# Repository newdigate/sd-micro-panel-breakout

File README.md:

# sd-micro panel-mount breakout/extender

## option 1 
 * https://github.com/dgouramanis/usdextendercable
   * Dean Gouramanis has done a much better job 
   * unforunately, nothing to mount pcb against front panel
   
## option 2
 * https://github.com/newdigate/usdextendercable
   * Based on the work above - I've extended the female board with 4 M2.5 mounting holes
 
## warning: untested concept work-in-progress, use with caution...

## why
I have a micro-controller mounted behind a front panel. The sd-card reader is fixed to the micro-controller board and is unaccessable to the user. I'd like to allow the user to access the sd-card reader via the front panel. 

I didn't have much success looking for panel mount sd-card extenders unfortunately. There does seems to be a micro-sd extender commonly available, but it doesnt seem to have any way to mount it at a right-angle on the front-panel.

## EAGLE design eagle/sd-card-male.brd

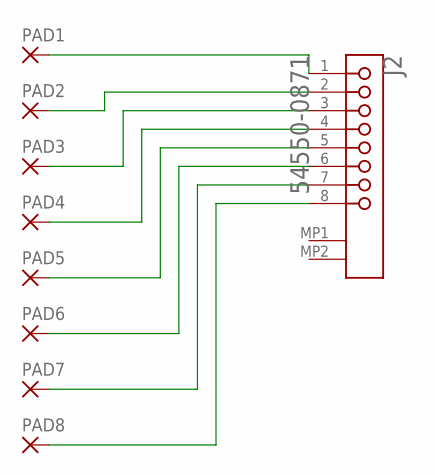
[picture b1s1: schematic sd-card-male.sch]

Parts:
J2: MOLEX_54550-0871MOLEX_54550-0871_0_0; MOLEX_54550-0871_0
PAD1, PAD2, PAD3, PAD5, PAD7, PAD8: SD_PAD_SMD_SHORT
PAD4, PAD6: SD_PAD_SMD_LONG

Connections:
unnamed: J2.1, PAD1.1
unnamed: J2.2, PAD2.1
unnamed: J2.3, PAD3.1
unnamed: J2.4, PAD4.1
unnamed: J2.5, PAD5.1
unnamed: J2.6, PAD6.1
unnamed: J2.7, PAD7.1
unnamed: J2.8, PAD8.1

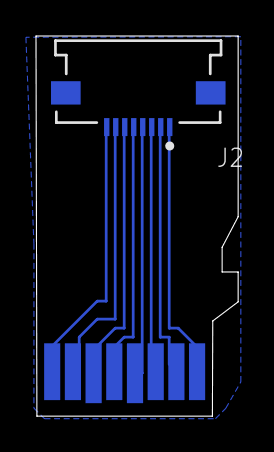
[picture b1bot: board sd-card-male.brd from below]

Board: 2 copper layers, 11.2 x 21.1 mm, 9 parts (9 on the bottom side), 8 nets.
